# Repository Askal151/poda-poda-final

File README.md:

# Poda-poda — Optical Card Organ ("Sun Organ")

Instrumen elektronik DIY: **kartu kaku berlubang** didorong di depan **cahaya alami** →
**LDR** per nada jadi gerbang optik → osilator **CD40106** (Schmitt) → mixer pasif → tone →
volume → **LM386** → jack aux 3.5mm. Handheld, engkol tangan, baterai 9V.
Konsep *Sun Organ*: cahaya alami = ekspresi dinamika (pitch tetap dikunci R·C).

*Poda* dalam bahasa Batak berarti nasihat atau ajaran. Bentuk lipatan akordeon pustaha laklak
dikombinasikan dengan kartu nada organ angin klasik; lubang nada diganti aksara Batak.
Dibuat saat residensi di Bitwäscherei, SGMK https://wiki.sgmk-ssam.ch/wiki/Main_Page

## Status
- 4 channel polifonik BUNYI di PCB etch — osilator + gerbang + amp + jack
- Schematic 4-channel SPICE-validated (`simulation/organ_spice.cir`)
- PCB single-sided, toner-transfer, solder tangan; DRC bersih (`docs/drc4.rpt`, 0 error/0 unconnected)
- Sisa: tuning pentatonik (4 nada, mis. C–D–E–G) + mekanik engkol/roller + casing

## Spesifikasi ringkas (4-channel)
- U1 = CD40106 (osilator, gate 1/2/4/5) · U2 = LM386 (amp)
- LDR1–4 (GL5528) · RV1–4 = trimpot 100k (pitch) · RV5 = 10k (volume)
- C timing = 47nF · R mixer = 10k · Zobel R6 10Ω + C10 0,47µF
- Attenuator R7 1k / R8 4,7k → level-line ke speaker aktif
- Peta gate: ch1 pin1/2 · ch2 pin3/4 · ch3 pin11/10 · ch4 pin9/8

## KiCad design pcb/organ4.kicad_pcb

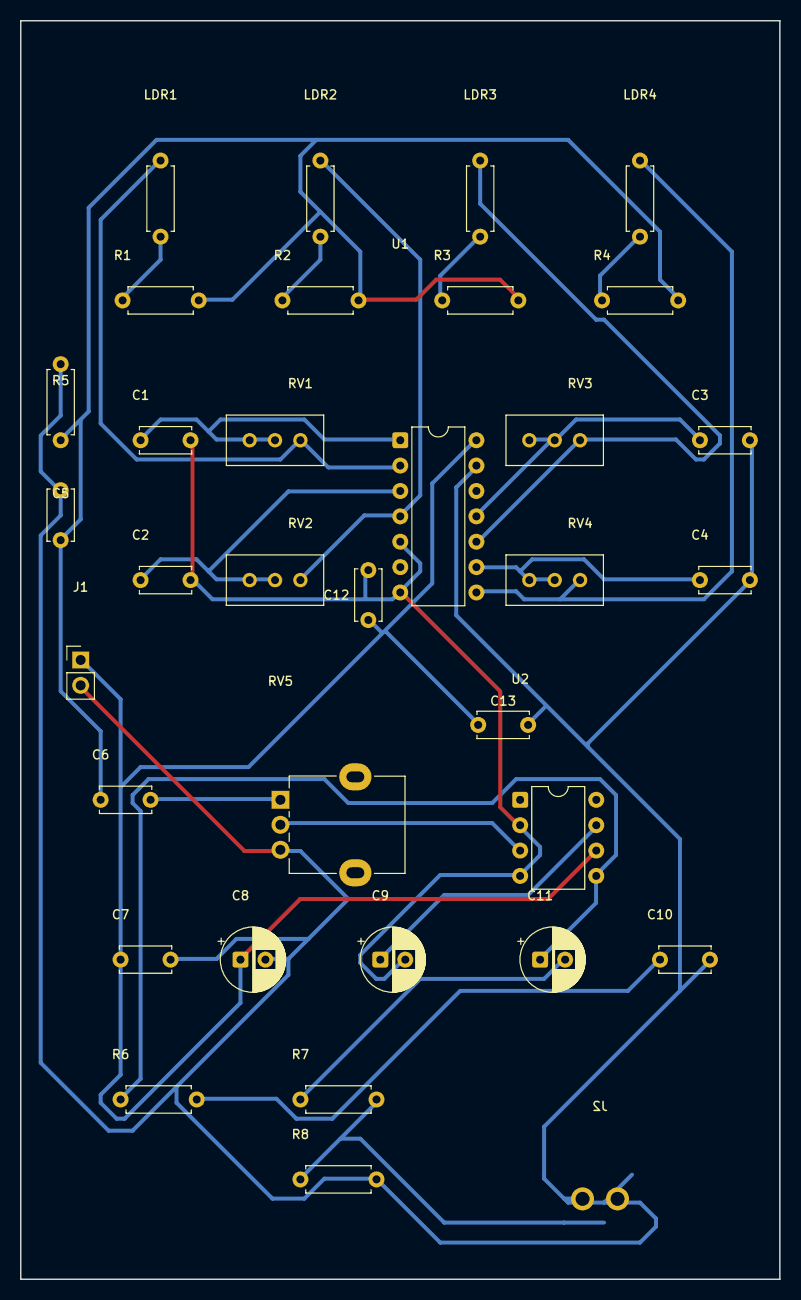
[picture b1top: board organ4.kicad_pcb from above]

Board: 2 copper layers, 76.0 x 126.0 mm, 34 parts (1 on the bottom side), 22 nets.

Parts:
C1, C2, C3, C4: 47nF; C_Disc_D5.0mm_W2.5mm_P5.00mm
C5: 10nF; C_Disc_D5.0mm_W2.5mm_P5.00mm
C6: 1uF; C_Disc_D5.0mm_W2.5mm_P5.00mm
C7, C12, C13: 0.1uF; C_Disc_D5.0mm_W2.5mm_P5.00mm
C8, C9, C11: 10uF; CP_Radial_D6.3mm_P2.50mm
C10: 0.47uF; C_Disc_D5.0mm_W2.5mm_P5.00mm
J1: Conn_01x02_Pin; PinHeader_1x02_P2.54mm_Vertical
J2: PJ-342
LDR1, LDR2, LDR3, LDR4: LDR; R_Axial_DIN0207_L6.3mm_D2.5mm_P7.62mm_Horizontal
R1, R2, R3, R4, R5: 10k; R_Axial_DIN0207_L6.3mm_D2.5mm_P7.62mm_Horizontal
R6: 10R; R_Axial_DIN0207_L6.3mm_D2.5mm_P7.62mm_Horizontal
R7: 1k; R_Axial_DIN0207_L6.3mm_D2.5mm_P7.62mm_Horizontal
R8: 4.7k; R_Axial_DIN0207_L6.3mm_D2.5mm_P7.62mm_Horizontal
RV1, RV2, RV3, RV4: 100k; Potentiometer_Bourns_3296W_Vertical
RV5: 10k; Potentiometer_Alpha_RD901F-40-00D_Single_Vertical
U1: 40106; DIP-14_W7.62mm
U2: LM386; DIP-8_W7.62mm

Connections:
+9V: C7.1, C8.1, C12.2, C13.1, J1.1, U1.14, U2.6
GND: C1.2, C2.2, C3.2, C4.2, C5.2, C7.2, C8.2, C9.2, C10.2, C12.1, C13.2, J1.2, J2.2, J2.6, J2.SH1, J2.SH2, R5.2, R8.2, RV5.3, U1.5, U1.7, U1.13, U2.2, U2.4
LM386_OUT: C11.1, R6.1, U2.5
unnamed: C1.1, RV1.2, RV1.3, U1.1
unnamed: LDR1.1, RV1.1, U1.2
unnamed: LDR1.2, R1.1
unnamed: C2.1, RV2.2, RV2.3, U1.3
unnamed: LDR2.1, RV2.1, U1.4
unnamed: LDR2.2, R2.1
unnamed: C3.1, RV3.2, RV3.3, U1.11
unnamed: LDR3.1, RV3.1, U1.10
unnamed: LDR3.2, R3.1
unnamed: C4.1, RV4.2, RV4.3, U1.9
unnamed: LDR4.1, RV4.1, U1.8
unnamed: LDR4.2, R4.1
unnamed: C9.1, U2.7
NODE_B: C11.2, R7.1
NODE_C: J2.3, J2.5, R7.2, R8.1
POT_TOP: C6.2, RV5.1
POT_WIPER: RV5.2, U2.3
SUMMING: C5.1, C6.1, R1.2, R2.2, R3.2, R4.2, R5.1
ZOBEL_MID: C10.1, R6.2

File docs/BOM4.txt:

Optical Card Organ - BOM (RefDes -> value)
==================================================
10k        x6  : R1, R2, R3, R4, R5, RV5
47nF       x4  : C1, C2, C3, C4
10nF       x1  : C5
100k       x4  : RV1, RV2, RV3, RV4
LDR        x4  : LDR1, LDR2, LDR3, LDR4
10uF       x3  : C11, C8, C9
0.47uF     x1  : C10
0.1uF      x3  : C7, C12, C13
10R        x1  : R6
1k         x1  : R7
1uF        x1  : C6
4.7k       x1  : R8
40106      x1  : U1
Conn_01x02_Pin x1  : J1
LM386      x1  : U2
PJ-342     x1  : J2
